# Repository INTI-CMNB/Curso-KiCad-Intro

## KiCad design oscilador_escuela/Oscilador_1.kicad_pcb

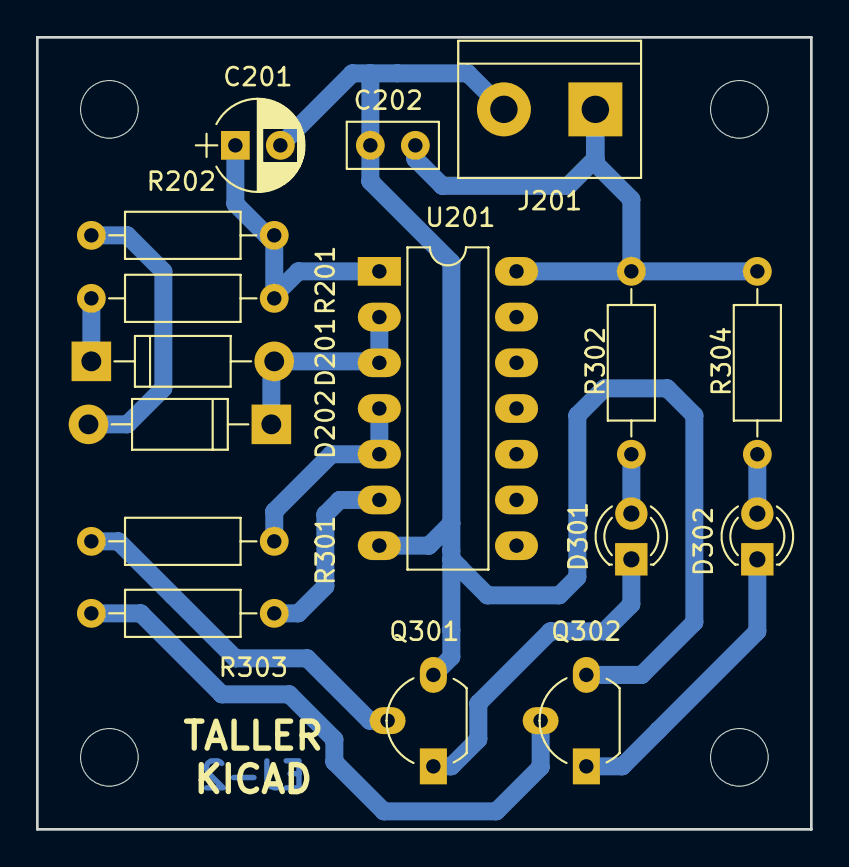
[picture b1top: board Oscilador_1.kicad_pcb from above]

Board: 2 copper layers, 43.0 x 44.0 mm, 20 parts (0 on the bottom side), 14 nets.

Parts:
C201: 1uF; CP_Radial_D5.0mm_P2.50mm
C202: 0.1u; C_Disc_D5.0mm_W2.5mm_P2.50mm
D201, D202: 1N4148; D_DO-41_SOD81_P10.16mm_Horizontal
D301: LED ROJO; LED_D3.0mm
D302: LED VERDE; LED_D3.0mm
J201: Conn_01x02; TerminalBlock_bornier-2_P5.08mm
MK101, MK102, MK103, MK104: Mounting_Hole; MountingHole_3.2mm_M3
Q301, Q302: BC546; TO-92_Molded_Wide_Oval
R201: 100k; R_Axial_DIN0207_L6.3mm_D2.5mm_P10.16mm_Horizontal
R202: 180k; R_Axial_DIN0207_L6.3mm_D2.5mm_P10.16mm_Horizontal
R301, R303: 2k2; R_Axial_DIN0207_L6.3mm_D2.5mm_P10.16mm_Horizontal
R302, R304: 470R; R_Axial_DIN0207_L6.3mm_D2.5mm_P10.16mm_Horizontal
U201: 40106; DIP-14_W7.62mm_LongPads

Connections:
+5V: C202.1, J201.1, R302.1, R304.1, U201.14
/Leds/LED1: R301.2, U201.4, U201.5
/Leds/LED2: R303.2, U201.6
/Oscilador/OSC: D201.2, D202.1, U201.2, U201.3
GND: C201.2, C202.2, J201.2, Q301.3, Q302.3, U201.7
unnamed: C201.1, R201.2, R202.2, U201.1
unnamed: D201.1, R201.1
unnamed: D202.2, R202.1
unnamed: D301.1, Q301.1
unnamed: D301.2, R302.2
unnamed: D302.1, Q302.1
unnamed: D302.2, R304.2
unnamed: Q301.2, R301.1
unnamed: Q302.2, R303.1

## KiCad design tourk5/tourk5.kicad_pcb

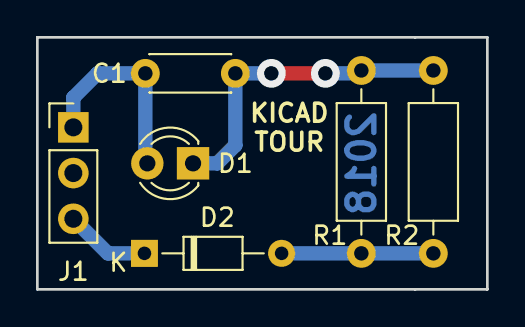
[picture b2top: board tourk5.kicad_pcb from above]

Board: 2 copper layers, 25.0 x 14.0 mm, 6 parts (0 on the bottom side), 4 nets.

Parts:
C1: 100nF; C_Disc_D4.3mm_W1.9mm_P5.00mm
D1: LED ROJO 3mm; LED_D3.0mm
D2: 1N4148; D_DO-34_SOD68_P7.62mm_Horizontal
J1: Conn_01x03; PinHeader_1x03_P2.54mm_Vertical
R1, R2: 100K; R_Axial_DIN0207_L6.3mm_D2.5mm_P10.16mm_Horizontal

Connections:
unnamed: C1.1, D1.1, R1.2, R2.2
unnamed: C1.2, D1.2, J1.1
unnamed: D2.1, J1.3
unnamed: D2.2, R1.1, R2.1
